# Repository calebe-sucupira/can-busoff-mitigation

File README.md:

# Throttling reativo em redes CAN

Projeto de Trabalho de Conclusão de Curso em Engenharia de Computação. Foram desenvolvidos firmwares, placas de circuito impresso e ferramentas de aquisição para avaliar o controle reativo de submissões CAN sob perturbações elétricas.

## O experimento

A bancada reúne dois nós ESP32-WROOM-32 com transceptores SN65HVD230, conectados a um barramento CAN clássico de **125 kbit/s**, e um injetor independente com Raspberry Pi Pico (RP2040) e transistor 2N2222. O Nó A produz e transmite as atualizações; o Nó B registra os quadros recebidos.

No Nó A, uma política de *throttling* usa o contador de erros de transmissão (TEC) para alterar a frequência nominal de novas submissões:

| Faixa de TEC | Modo | Taxa nominal |
| --- | --- | ---: |
| 0–95 | Normal | 100 Hz |
| 96–127 | Alerta | 50 Hz |
| 128 ou mais | Crítico | 25 Hz |

A produção da aplicação continua em **100 Hz**. Uma fila de uma posição mantém somente a atualização mais recente (*latest-only*). A política não modifica a retransmissão automática do controlador. A mesma base de firmware é utilizada na condição de referência (`ENABLE_THROTTLING=0`) e na condição reativa (`ENABLE_THROTTLING=1`), por meio de configurações distintas de compilação.

## Resultados

Foram realizados **100 ensaios** em dois conjuntos:

- **60 ensaios de caracterização:** três densidades de perturbação e duas condições de operação, com dez repetições por grupo. Nenhum atingiu Bus-Off. No perfil de maior densidade, a política reduziu o número de atualizações efetivamente entregues.
- **40 ensaios de progressão até Bus-Off:** 20 por condição. Todos alcançaram Bus-Off. O tempo médio foi de **10,39 s** na referência e **12,08 s** na condição reativa. A comparação estatística não foi significativa (Mann–Whitney bilateral, `p ≈ 0,285`).

No segundo anterior ao Bus-Off, a média de transmissões concluídas foi de **97,2** na referência e **28,7** na condição reativa, redução aproximada de **70,5%**. A contenção do tráfego foi observada, mas **não foi demonstrado que a política evita ou retarda de forma consistente o Bus-Off**. A menor frequência de atualizações recebidas é um custo da estratégia.

## Estrutura do repositório

| Pasta | Conteúdo |
| --- | --- |
| `firmware/node-a/` | Firmware transmissor e política reativa |
| `firmware/node-b/` | Firmware receptor |
| `firmware/pico-injector/` | Firmware parametrizável do injetor (caracterização) |
| `hardware/` | Projetos KiCad das duas placas e bibliotecas |
| `experiments/characterization/` | Executores e planos dos 60 ensaios |
| `experiments/busoff/` | Código e plano dos 40 ensaios de progressão |
| `data/` | ZIPs dos 100 ensaios definitivos e dos dois pilotos de segurança da campanha Bus-Off |
| `docs/` | Documentação de fabricação e compilação |

O código do injetor para a campanha de progressão até Bus-Off está em `experiments/busoff/main_phase20.c` e `experiments/busoff/injector.pio`; é distinto do firmware parametrizável da caracterização.

A campanha de Bus-Off também utilizou uma variante do firmware do Nó A com registros adicionais de telemetria. Seu código-fonte está preservado em `experiments/busoff/node_a_busoff_trace.c`, identificado nos logs pelo marcador `node-a-throttling-v1.3-busoff-trace`. O `firmware/node-a/` permanece como base geral do projeto.

Os 60 ensaios compreendem as execuções **153–188** e **197–220**, armazenadas individualmente em `data/zips/`. Os 40 ensaios de progressão compreendem **304–343**, armazenados em `data/busoff_estudo_2026/zips/`. Os ZIPs incluem os arquivos de log, CSVs, metadados e controle de qualidade originais. As cópias descompactadas foram removidas para evitar duplicação. Os ZIPs dos pilotos **300 e 303** também foram mantidos porque o orquestrador os verifica antes da execução física; não integram a amostra de 40.

Veja [experiments/README.md](experiments/README.md) para localizar os programas e planos. Para compilar a partir de um clone limpo, consulte [docs/reproducao.md](docs/reproducao.md).

## Tecnologias

ESP-IDF 6.0.2, FreeRTOS, Raspberry Pi Pico SDK, PIO, C, Python 3 (pyserial) e KiCad.

A compilação e a execução exigem as ferramentas e configurações de cada placa. Não se deve executar campanhas físicas sem conferir previamente as conexões, o circuito de injeção e os mecanismos de interrupção.

## Limitações e segurança

O circuito injetor comuta temporariamente CAN_H e CAN_L. Foi desenvolvido **exclusivamente para uma bancada isolada**; não se destina à injeção de falhas em veículos ou equipamentos em operação. A parada controlada por software não substitui a possibilidade de desenergização física.

Os resultados se referem à configuração experimental descrita; não estabelecem parâmetros ótimos para outras redes CAN.

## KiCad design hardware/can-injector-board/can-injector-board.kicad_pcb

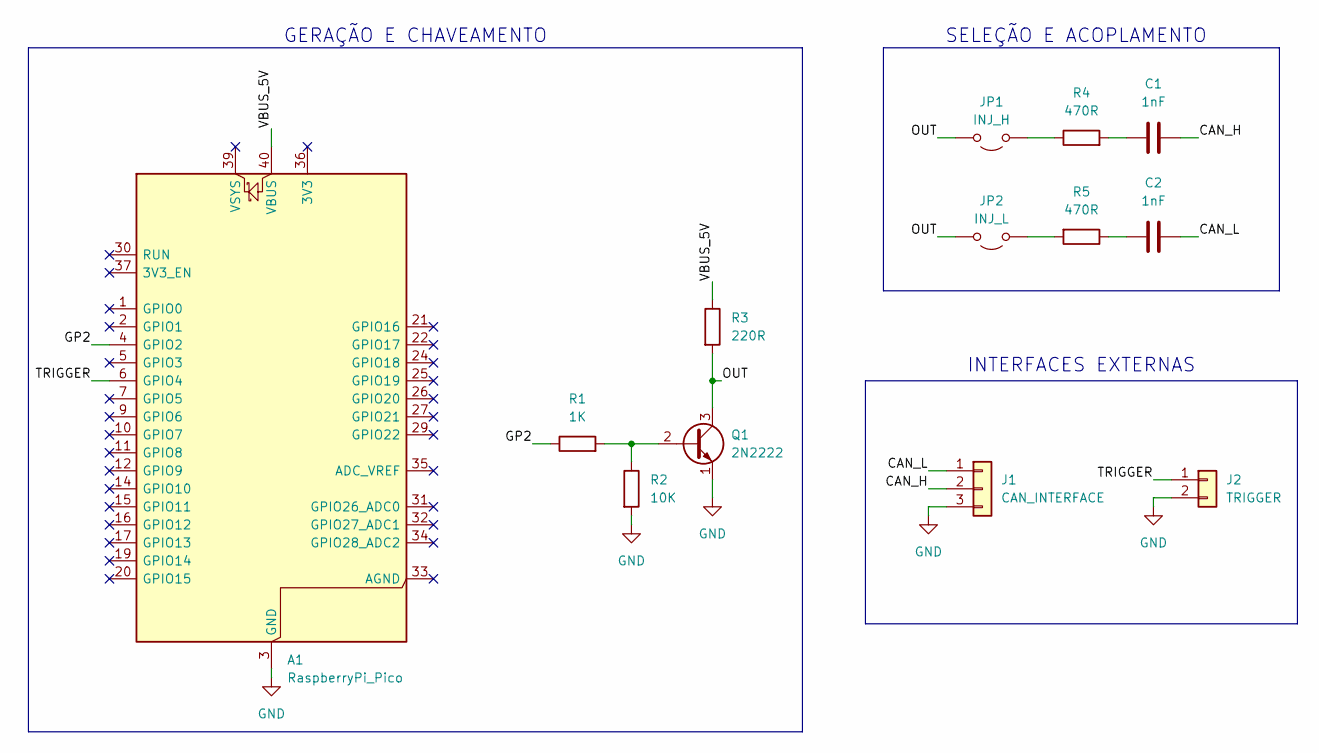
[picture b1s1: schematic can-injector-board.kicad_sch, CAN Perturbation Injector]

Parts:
A1: RaspberryPi_Pico; RaspberryPi_Pico_Common_THT_Manual
C1, C2: 1nF; C_Disc_D5.0mm_W2.5mm_P5.00mm_Manual
J1: CAN_INTERFACE; PinHeader_1x03_P2.54mm_Vertical_Manual
J2: TRIGGER; PinHeader_1x02_P2.54mm_Vertical_Manual
JP1: INJ_H; PinHeader_1x02_P2.54mm_Vertical_Manual
JP2: INJ_L; PinHeader_1x02_P2.54mm_Vertical_Manual
Q1: 2N2222; TO-92_Inline_Wide_Manual
R1: 1K; R_Axial_DIN0207_L6.3mm_D2.5mm_P7.62mm_Horizontal_Manual
R2: 10K; R_Axial_DIN0207_L6.3mm_D2.5mm_P7.62mm_Horizontal_Manual
R3: 220R; R_Axial_DIN0207_L6.3mm_D2.5mm_P7.62mm_Horizontal_Manual
R4, R5: 470R; R_Axial_DIN0207_L6.3mm_D2.5mm_P7.62mm_Horizontal_Manual

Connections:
/CAN_H: C1.2, J1.2
/CAN_L: C2.2, J1.1
/GP2: A1.4 (GPIO2), R1.1
/OUT: JP1.2 (B), JP2.2 (B), Q1.3 (C), R3.2
/TRIGGER: A1.6 (GPIO4), J2.1
/VBUS_5V: A1.40 (VBUS), R3.1
GND: A1.3 (GND), A1.8 (GND), A1.13 (GND), A1.18 (GND), A1.23 (GND), A1.28 (GND), A1.38 (GND), J1.3, J2.2, Q1.1 (E), R2.2
unnamed: C1.1, R4.2
unnamed: C2.1, R5.1
unnamed: JP1.1 (A), R4.1
unnamed: JP2.1 (A), R5.2
unnamed: Q1.2 (B), R1.2, R2.1

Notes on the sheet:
GERAÇÃO E CHAVEAMENTO
INTERFACES EXTERNAS
SELEÇÃO E ACOPLAMENTO

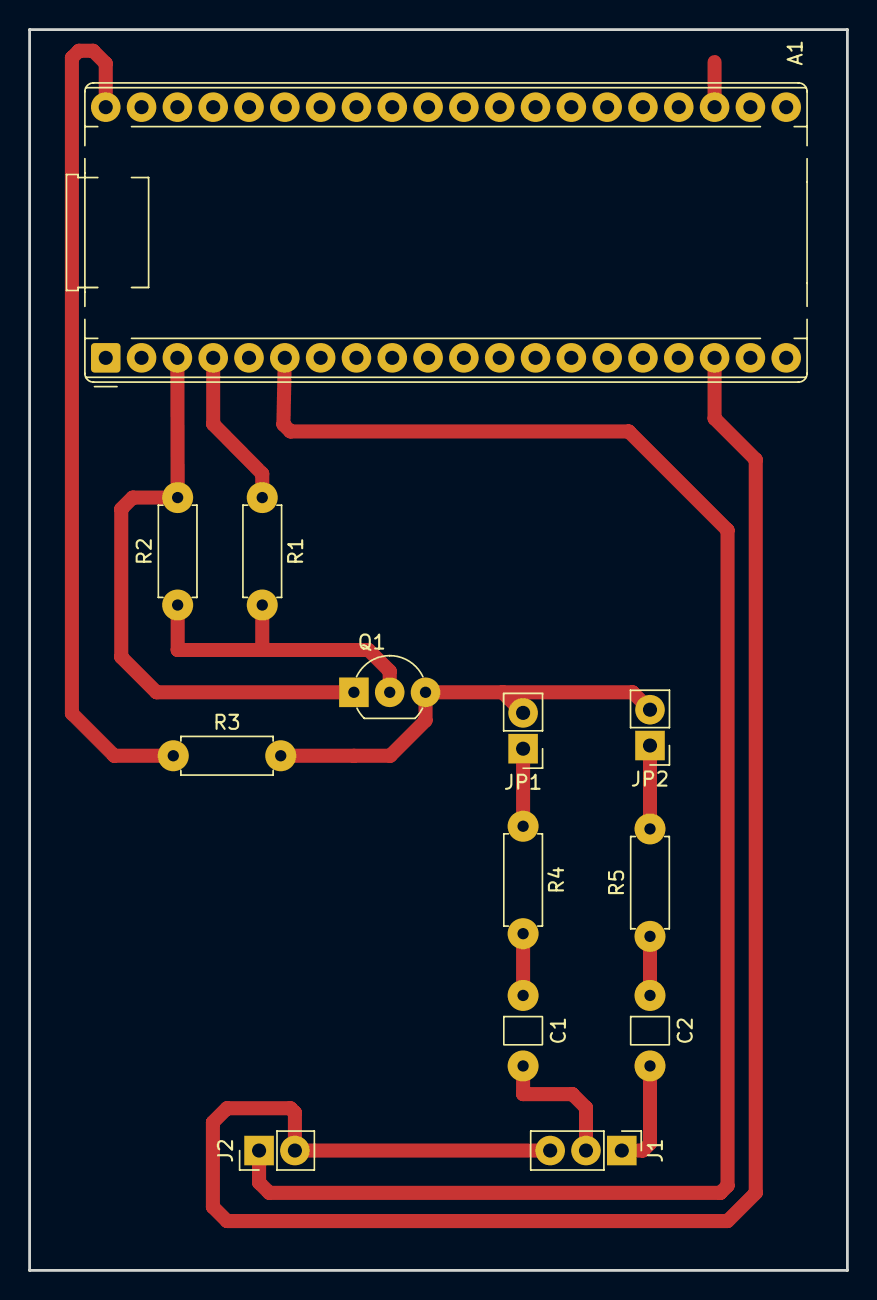
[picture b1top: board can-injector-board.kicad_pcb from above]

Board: 2 copper layers, 58.0 x 88.0 mm, 13 parts (0 on the bottom side), 12 nets.

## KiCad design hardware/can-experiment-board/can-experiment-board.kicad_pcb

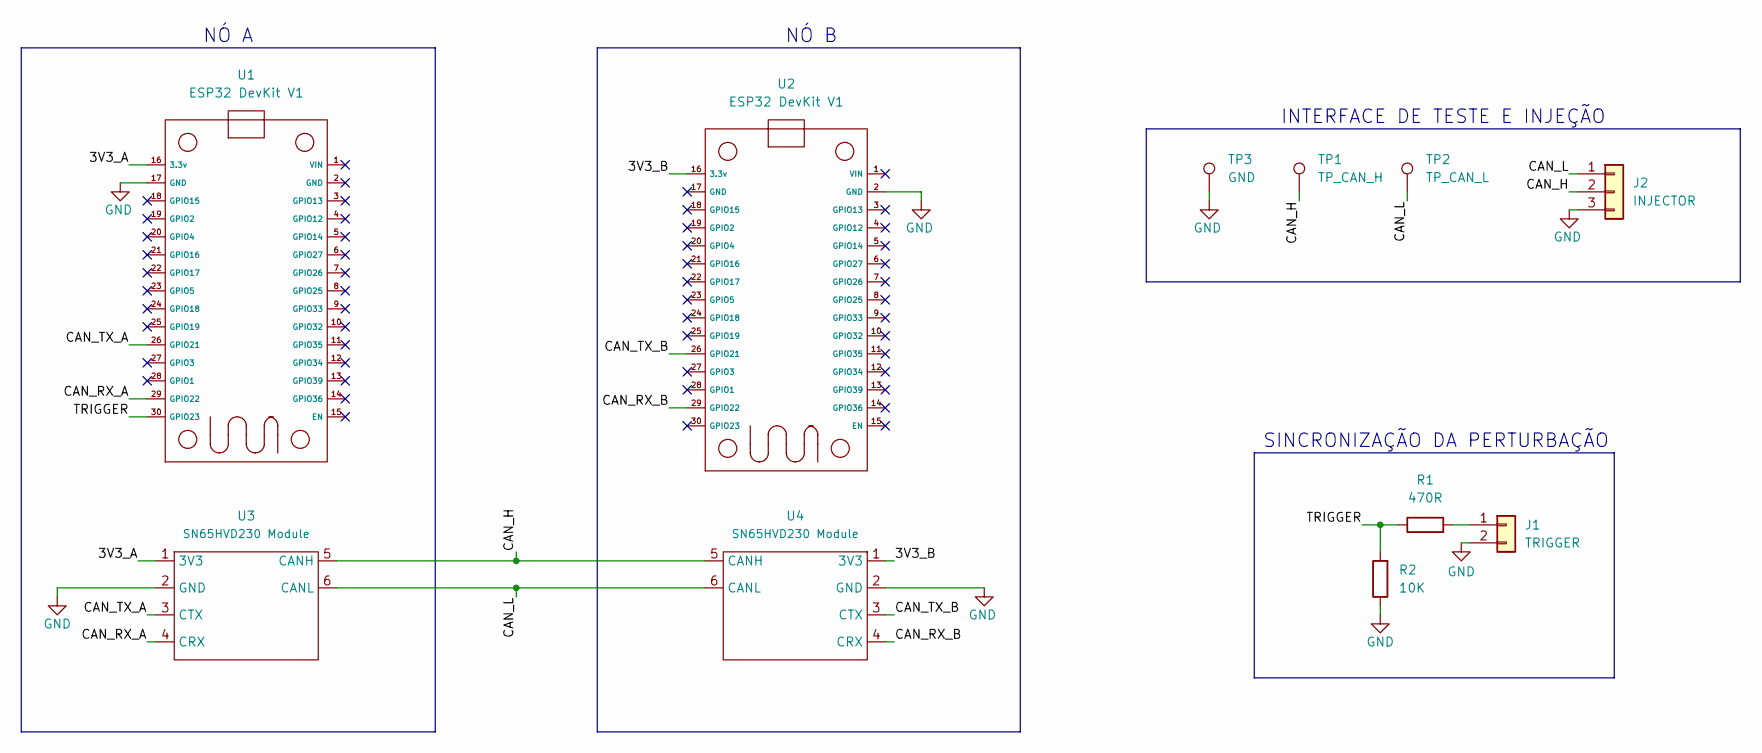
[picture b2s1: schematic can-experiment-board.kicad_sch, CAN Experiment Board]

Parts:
J1: TRIGGER; PinHeader_1x02_P2.54mm_Vertical_Manual
J2: INJECTOR; PinHeader_1x03_P2.54mm_Vertical_Manual
R1: 470R; R_Axial_DIN0207_L6.3mm_D2.5mm_P7.62mm_Horizontal_Manual
R2: 10K; R_Axial_DIN0207_L6.3mm_D2.5mm_P7.62mm_Horizontal_Manual
TP1: TP_CAN_H; TestPoint_THTPad_D2.5mm_Drill1.2mm
TP2: TP_CAN_L; TestPoint_THTPad_D2.5mm_Drill1.2mm
TP3: GND; TestPoint_THTPad_D2.5mm_Drill1.2mm
U1, U2: ESP32 DevKit V1; ESP32_30pin_Manual
U3, U4: SN65HVD230 Module; SN65HVD230_Module_1x06_Manual

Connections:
/3V3_A: U1.16 (3.3v), U3.1 (3V3)
/3V3_B: U2.16 (3.3v), U4.1 (3V3)
/CAN_H: J2.2, TP1.1 (1_1), U3.5 (CANH), U4.5 (CANH)
/CAN_L: J2.1, TP2.1 (1_1), U3.6 (CANL), U4.6 (CANL)
/CAN_RX_A: U1.29 (GPIO22), U3.4 (CRX)
/CAN_RX_B: U2.29 (GPIO22), U4.4 (CRX)
/CAN_TX_A: U1.26 (GPIO21), U3.3 (CTX)
/CAN_TX_B: U2.26 (GPIO21), U4.3 (CTX)
/TRIGGER: R1.1, R2.2, U1.30 (GPIO23)
GND: J1.2, J2.3, R2.1, TP3.1 (1_1), U1.17 (GND), U2.2 (GND), U3.2 (GND), U4.2 (GND)
unnamed: J1.1, R1.2

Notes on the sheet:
NÓ A
NÓ B
SINCRONIZAÇÃO DA PERTURBAÇÃO
INTERFACE DE TESTE E INJEÇÃO

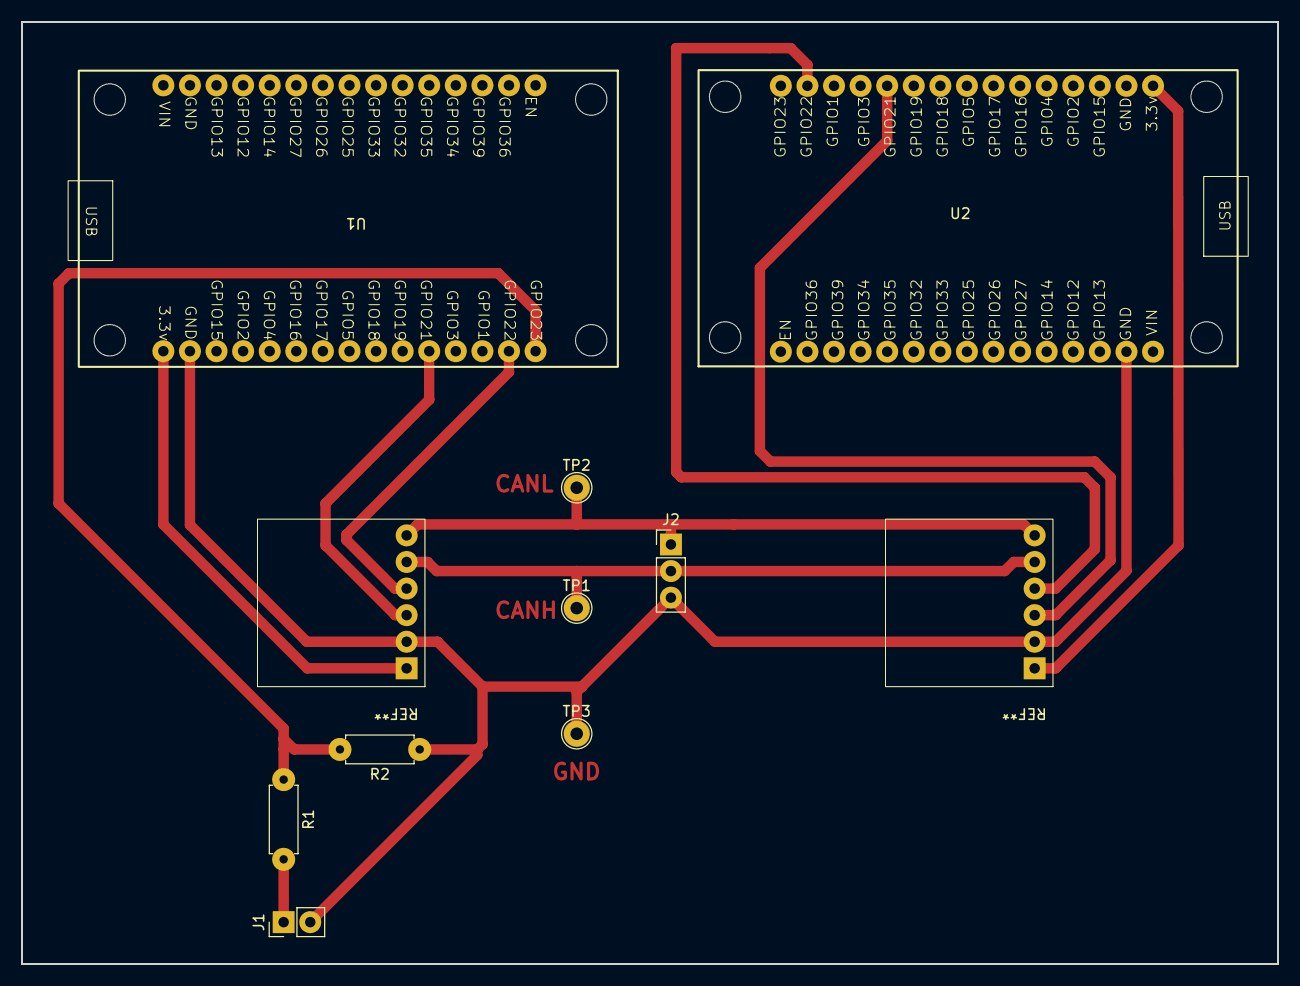
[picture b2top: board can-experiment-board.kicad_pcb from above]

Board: 2 copper layers, 120.0 x 90.0 mm, 11 parts (0 on the bottom side), 11 nets.
